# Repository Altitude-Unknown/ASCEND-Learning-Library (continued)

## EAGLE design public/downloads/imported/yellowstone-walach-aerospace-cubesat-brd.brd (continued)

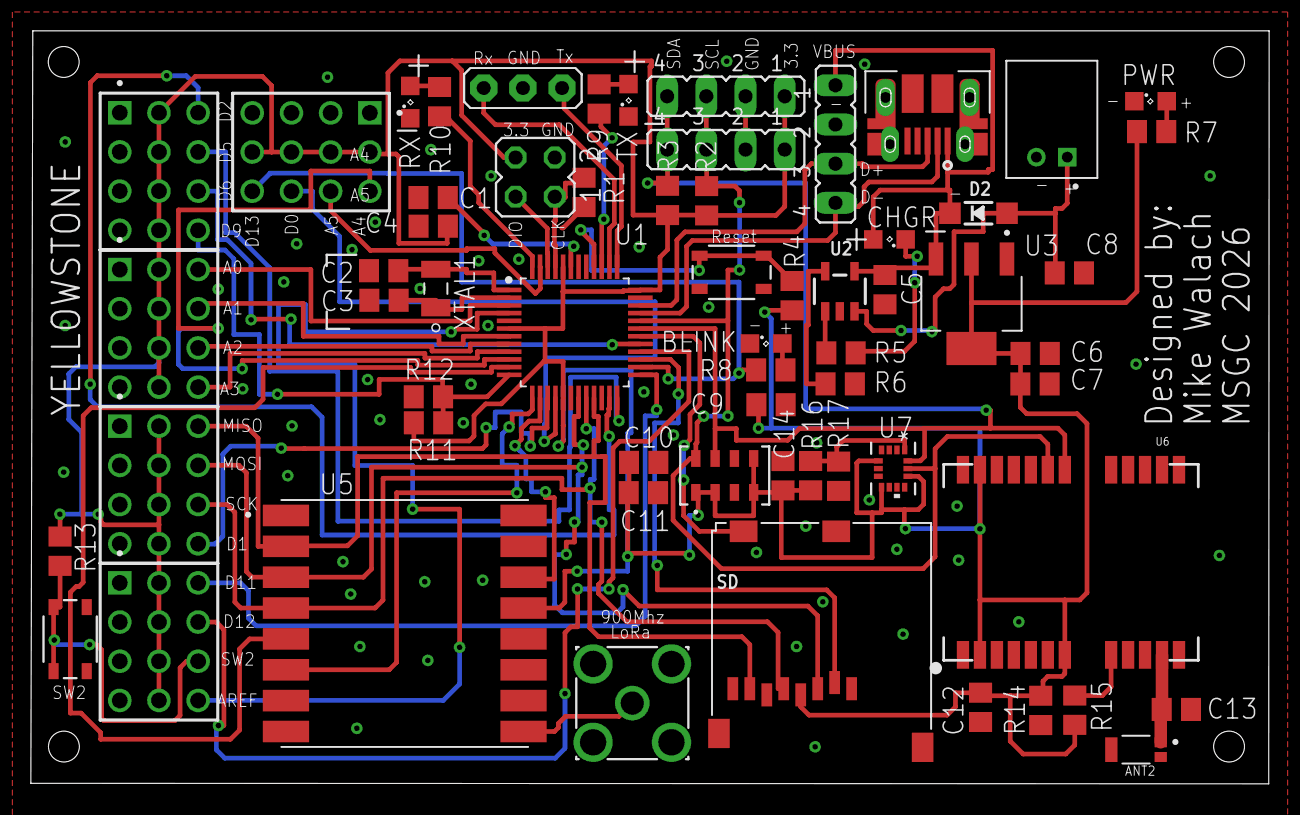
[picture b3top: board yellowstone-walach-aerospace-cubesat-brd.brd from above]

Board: 2 copper layers, 80.3 x 48.8 mm, 62 parts (0 on the bottom side), 54 nets.
